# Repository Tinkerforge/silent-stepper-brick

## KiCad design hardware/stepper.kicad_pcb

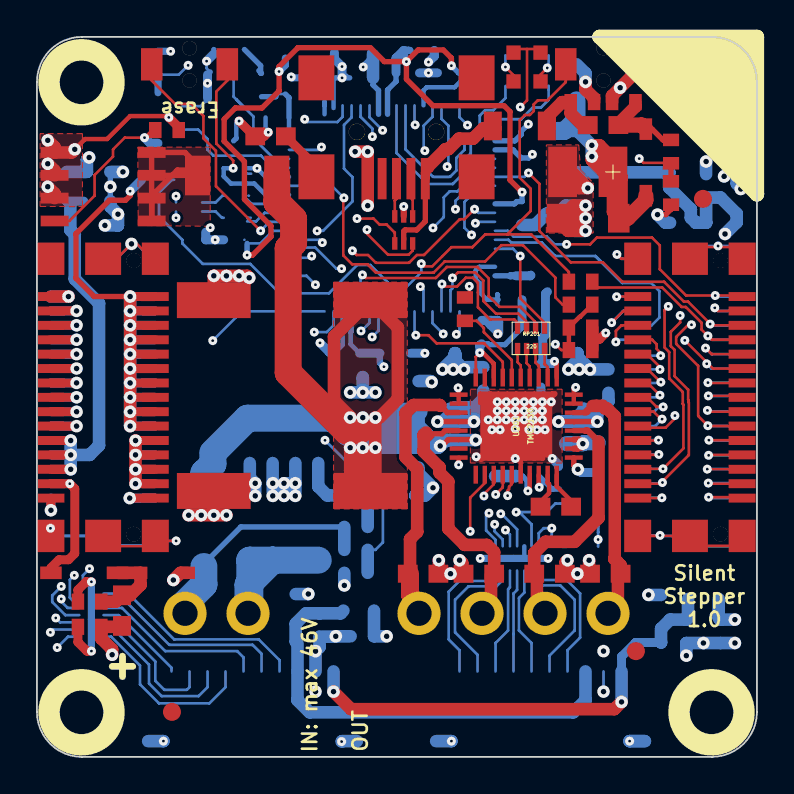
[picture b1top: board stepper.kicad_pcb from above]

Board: 6 copper layers, 40.0 x 40.0 mm, 129 parts (0 on the bottom side), 129 nets.

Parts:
C101, C102, C301, C302, C303, C304, C401, C402, C403, C404: 1µF; C0402E
C103, C104: DNP; C0402E
C201, C209, C217, C218, C503, C506, C507, C508, C510, C511, C512, C513, C515, C517, C518: 100nF; C0402E
C202, C205: 330µF/50V; ELKO_103
C203: 470nF; C0402E
C204, C505, C516: 4.7µF; C0603E
C206, C208, C211, C213: 100nF/50V; C0603E
C207: 22nF/50V-low; C0603E
C210, C212, C214, C216: 470pF/100V; C0603E
C215: 4.7µF/50V; C1206
C501: 100µF; 3528-21
C502, C504: 10µF; C0805
C509: 2.2µF; C0603E
C514: 10µF/10V; C0805
D101: blue; D0603
D102: red; D0603
D201: Z12V; SOD-123
D202, D203: PMEG6045ETPX; SOD-128
D301, D402: ESD5V0D3B-TP; SOD-323
D302: ESD3V3D3B-TP; SOD-323
D401: TVS 3V3; SOD-323
D403, D501: B0520LW-7-F; SOD-123
D502: Z5V; MiniMelf
D503: Z3.3V; MiniMelf
F101: PTC; C1206
FB101, FB102, FB401, FB402: FB; C0603E
FB301, FB302: FILTER; C0603E
FILTER301, FILTER302: Filter-8x; DFN16-33x135
Fiducial_Mark: VAL**; Fiducial_Mark
Fiducial_Mark#2, Fiducial_Mark#3, Fiducial_Mark#4, Fiducial_Mark#5, Fiducial_Mark#6: VAL**; Fiducial_Mark
J101: USB-MINI-B-SMD
J102, J103, J104, J105: DRILL; DRILL_NP
J401, J403: STACK-UP-HIGH; BTB08-ACS-TOP
J402, J404: STACK-DOWN; BTB08-ACS-BTM
L101: 744230900; WE-CNSW-0603
L501: LBR2012T100K; C0805
P201: black; OQ_2P
P202: green; OQ_4P
P301, P302: CON-SENSOR
Q201: AO4438; SOIC-8-MOSFET
Q202: AO4421; SOIC-8-MOSFET
Q203: 2N7002; SOT23GDS
R101, R102: 27; R0402E
R103: 1.8k; R0402E
R104: 2.7k; R0402E
R105: 100; R0402E
R201, R203, R207, R208, R210, R213, R401: 1k; R0402E
R202, R204, R206: 10k; R0402E
R205: 100k; R0402E
R209: FB; C0402E
R211: 2R2; R0402E
R212: 3.9k; R0402E
R214, R215: 0.12/0.5W; R1206
R216: 220; R0402E
R501: 1R0; R0402E
RP101, RP301: 1k; 4X0603
RP201: 220; 4X0402
SW101: Reset; TACT-SWITCH
SW102: Erase; TACT-SWITCH
U101: AT91SAM3SXB; LQFP64
U102: 82400152; SOT563-SPEC
U201: TMC2130; QFN36_5X6
U501: LD1117; SOT-223
VAL: WEEE_7mm_back
VAL#2: CE_5mm
X101: 16Mhz; CRYSTAL_3225

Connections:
3V3: C302.1, C401.1, C502.1, C503.1, C505.1, C506.1, C507.1, C508.1, C514.1, C515.1, C518.1, D101.1, D102.1, D503.2, FB302.1, FB401.1, FILTER301.14, J401.20, RP301.1, RP301.2, RP301.3, RP301.4, SW102.2, U101.1, U101.7, U101.18, U101.45, U101.58, U501.2
BRICKLET-I2C-SCL: FILTER301.16, FILTER302.16, RP301.8, U101.36
BRICKLET-I2C-SDA: FILTER301.15, FILTER302.15, RP301.5, U101.43
BRICKLET-IO0_0/AD0: FILTER301.10, U101.3
BRICKLET-IO0_1: FILTER301.11, U101.5
BRICKLET-IO0_2/PWM0: FILTER301.12, U101.48
BRICKLET-IO0_3: FILTER301.13, U101.25
BRICKLET-IO1_0/AD1: FILTER302.13, U101.4
BRICKLET-IO1_1: FILTER302.12, U101.6
BRICKLET-IO1_2/PWM1: FILTER302.11, U101.47
BRICKLET-IO1_3: FILTER302.10, U101.19
M1: C216.2, P202.1, U201.13
M2: C214.2, P202.2, U201.15
M3: C212.2, P202.3, U201.32
M4: C210.2, P202.4, U201.34
unnamed: C102.1, F101.1, FB101.2
unnamed: C201.2, R209.2, R210.1, U201.8, U201.10
unnamed: C203.1, R211.1, U201.26
unnamed: C204.1, R211.2, U201.25
unnamed: C207.1, U201.27
unnamed: C207.2, U201.28
unnamed: C208.2, U201.29
unnamed: C209.2, R212.1, R213.2, U201.23
unnamed: C217.2, R214.2, U201.14
unnamed: C218.2, R215.2, U201.33
unnamed: C303.1, D301.2, FB301.2, P301.1, P302.1
unnamed: C304.1, D302.2, FB302.2, P301.3, P302.3
unnamed: C403.1, D401.2, D403.1, FB401.2
unnamed: C404.1, D402.2, FB402.2, J403.22, J403.24, J403.26, J404.22, J404.24, J404.26
unnamed: C509.1, C510.1, C511.1, C512.1, C513.1, L501.1, U101.8, U101.12, U101.24, U101.54
unnamed: C516.1, R501.1
unnamed: C517.1, L501.2, R501.2, U101.64
unnamed: D101.2, RP101.1
unnamed: D102.2, RP101.4
unnamed: D201.2, Q201.G, R205.2
unnamed: D202.1, Q202.D
unnamed: D203.1, P201.1, R205.1, R206.1
unnamed: D403.2, J403.28, J404.28
unnamed: F101.2, J101.1, U102.5
unnamed: FB102.2, J101.6
unnamed: FILTER301.1, P301.4
unnamed: FILTER301.2, P301.5
unnamed: FILTER301.3, P301.6
unnamed: FILTER301.4, P301.10
unnamed: FILTER301.5, P301.9
unnamed: FILTER301.6, P301.8
unnamed: FILTER301.7, P301.7
unnamed: FILTER302.1, P302.4
unnamed: FILTER302.2, P302.5
unnamed: FILTER302.3, P302.6
unnamed: FILTER302.4, P302.7
unnamed: FILTER302.5, P302.8
unnamed: FILTER302.6, P302.9
unnamed: FILTER302.7, P302.10
unnamed: J101.2, U102.1
unnamed: J101.3, U102.3
unnamed: J401.6, J402.8
unnamed: J401.7, J402.7, R401.1
unnamed: J401.8, J402.10
unnamed: J401.10, J402.12
unnamed: J401.12, J402.14
unnamed: J401.13, J402.13
unnamed: J401.14, J402.16
unnamed: J401.15, J402.15
unnamed: J401.16, J402.18
unnamed: J401.17, J402.17
unnamed: J401.18, J402.20
unnamed: J401.21, J402.21
unnamed: J401.22, J402.22
unnamed: J401.23, J402.23
unnamed: J401.24, J402.24
unnamed: J401.25, J402.25
unnamed: J401.27, J402.27
unnamed: J401.29, J402.29
unnamed: J401.30, J402.30
unnamed: J403.29, J404.29
unnamed: J403.30, J404.30
unnamed: L101.1, R102.1
unnamed: L101.2, U102.4
unnamed: L101.3, U102.6
unnamed: L101.4, R101.1
unnamed: P201.2, Q201.D
unnamed: Q202.G, Q203.D, R204.1
unnamed: R101.2, U101.56
unnamed: R102.2, U101.57
unnamed: R105.1, U101.32
unnamed: R216.2, U201.6
unnamed: RP101.5, U101.10
unnamed: RP101.8, U101.9
unnamed: RP201.5, U201.5
unnamed: RP201.6, U201.4
unnamed: RP201.7, U201.3
unnamed: RP201.8, U201.2
unnamed: SW102.1, U101.55
PWR-CLK: R105.2, R201.1, U201.1
PWR-CS: RP201.1, U101.29
PWR-DAC-VREF: R213.1, U101.59
PWR-DIAG0: U101.52, U201.20
PWR-DIAG1: U101.42, U201.21
PWR-DIR: U101.38, U201.7
PWR-ENABLE: U101.37, U201.22
PWR-SCK: RP201.2, U101.44
PWR-SDI: RP201.3, U101.34
PWR-SDO: RP201.4, U101.35
PWR-STEP: R216.1, U101.20
PWR-SW-3V3: R209.1, U101.31
PWR-VEXT: R206.2, R207.1, U101.13
PWR-VSTACK: R202.2, R203.1, U101.16
PWR-VSTACK-SW: Q203.G, R208.2, U101.41
STACK-DETECT/JTAG-TMS: J401.9, J402.9, U101.51
STACK-I2C-SCL/JTAG-TDO: J401.4, J402.4, U101.49
STACK-I2C-SDA/JTAG-TDI: J401.2, J402.2, U101.33
STACK-INT: J401.19, J402.19, U101.63
STACK-PGND: C101.2, C102.2, C103.2, C104.2, C201.1, C202.2, C203.2, C204.2, C205.2, C206.2, C209.1, C210.1, C211.2, C212.1, C213.2, C214.1, C215.2, C216.1, C217.1, C218.1, C301.2, C302.2, C303.2, C304.2, C401.2, C402.2, C403.2, C404.2, C501.2, C502.2, C503.2, C504.2, C505.2, C506.2, C507.2, C508.2, C509.2, C510.2, C511.2, C512.2, C513.2, C514.2, C515.2, C516.2, C517.2, C518.2, D201.1, D301.1, D302.1, D401.1, D402.1, D502.1, D503.1, FB102.1, FILTER301.EXP, FILTER302.14, FILTER302.EXP, J101.5, J401.EP, J402.EP, J403.1, J403.3, J403.5, J403.7, J403.9, J403.11, J403.13, J403.15, J403.17, J403.19, J403.21, J403.23, J403.25, J403.27, J403.EP, J404.1, J404.3, J404.5, J404.7, J404.9, J404.11, J404.13, J404.15, J404.17, J404.19, J404.21, J404.23, J404.25, J404.27, J404.EP, P301.2, P301.EP, P302.2, P302.EP, Q201.S, Q203.S, R104.1, R201.2, R203.2, R207.2, R208.1, R210.2, R212.2, R214.1, R215.1, SW101.2, U101.2, U101.17, U101.46, U101.60, U102.2, U201.11, U201.12, U201.18, U201.24, U201.35, U201.36, U201.EXP, U501.1, X101.3
STACK-PVCC: J403.2, J403.4, J403.6, J403.8, J403.10, J403.12, J403.14, J403.16, J403.18, J403.20, J404.2, J404.4, J404.6, J404.8, J404.10, J404.12, J404.14, J404.16, J404.18, J404.20, Q202.S, R202.1, R204.2
STACK-RESET: R401.2, SW101.1, U101.39
STACK-SER-RXD: J401.26, J402.26, U101.11
STACK-SER-TXD: J401.28, J402.28, U101.14
STACK-SPI-MISO: J401.1, J402.1, U101.27
STACK-SPI-MOSI: J401.3, J402.3, U101.22
STACK-SPI-SCLK: J401.5, J402.5, U101.21
STACK-SPI-SELECT: J402.6, U101.28
STACK-SYNC/JTAG-TCK: J401.11, J402.11, U101.53
USB-DETECT: R103.2, R104.2, U101.26
VEE: C202.1, C205.1, C206.1, C208.1, C211.1, C213.1, C215.1, D202.2, D203.2, U201.16, U201.30, U201.31
VSTACK: C301.1, C402.1, C501.1, C504.1, D501.2, D502.2, FB301.1, FB402.1, U501.3
VUSB: C101.1, D501.1, FB101.1, R103.1
XIN: C104.1, U101.62, X101.2
XOUT: C103.1, U101.61, X101.1

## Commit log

2015-09-15 add hardware files of silent stepper brick prototype
2015-09-15 add datasheet of TMC2100 and copied and modified stepper firmware
2015-09-16 working demo, configuration hardcoded
2015-11-26 fix text positions
2015-12-17 minor changes
2015-12-17 Fix names, versions, etc
2015-12-23 Add Silent Stepper configuration API
2016-02-08 update to new library settings
2016-02-09 fix tf logo, remove current measurement
2016-02-09 missing commit, remove current measurement
2016-02-09 Add WIP marker
2016-02-09 Add .gitignore
2016-02-11 fix wrong bricklet select voltages
2016-02-11 detail routing improvements
2016-02-12 move leds from border, delete to near doku
2016-02-22 fix led config
2016-02-24 remove motor capacitors
2016-02-25 uncomitted hardware changes
2016-02-25 remove cfg3, add clk connection, imprv gnd routing, 3v3 switchable
2016-06-13 demo stepper mode switching
2016-06-22 changed to tmc2130
2016-09-06 mark: remove 3v3 mosfet
2016-09-16 Basic adjustments for SPI configuration
2016-09-28 Seperate TCM2130 configuration from general stepper handling
2016-09-28 Implement stepping for dedge=1
2016-09-28 Remove unused function declarations
2016-10-04 remove unnecessary signals, add external clock
2016-10-05 change driver type to tmc2130
2016-10-13 Make register write async
2016-10-14 Disable DMA support for now (not working)
2016-10-17 change clock series resistor 1k->470
2016-10-18 Add driver status support
2016-10-21 Handle spi read overrun
2016-10-21 turn DMA off after deselect
2016-10-21 Properly handle enable pin after active changes from false to true
2016-10-21 Add active pin handle variables
2016-11-24 Remove unused function
2016-11-25 swap pins, add series resistors, add clock pi filter
2016-12-02 add pdfs
2016-12-05 Add system timer utility file include to Makefile
2016-12-06 adapt software to current hardware version Change pins of: * leds * spi cs * enable pins
2016-12-15 version before changing to 6 layers
2016-12-15 change to 6 layer layout
2016-12-16 change routing, remove pi filter
2016-12-19 drc check
2017-01-06 Add COM_MESSAGE_USER_LAST_FID define (needed for newest bricklib)
2017-01-09 update fiducials
2017-01-17 change default design to 6layer design
2017-01-26 Add human readable parameters for basic config function
2017-01-26 Use correct delay for one second at 12.8MHz
2017-01-26 Add current output default value (800mA)
2017-01-26 Remove obsolete FIXME comment
2017-01-26 Use correct VREF scaling for maximum current configuration
2017-04-18 add schematics
2017-04-19 The driver IC is called TMC2130, not TCM2130...
2017-04-19 Fix typo
2017-04-19 Remove debug
2017-04-19 Add examples
2017-04-21 Fix examples
2017-04-21 Add 3d information (tbc)
2017-04-21 Add most of the 3d information
2017-04-25 Change D102 to red 3d model
2017-04-25 Change connection footprints
2017-04-28 Fix reordered component paths
2017-04-28 Add Elkos and 4x0603 3d models
2017-05-11 Add support for co-mcu Bricklets
2017-05-11 Add changelog
2017-05-11 Fix changelog
2017-05-16 Remove bogus stepper current calculation.
    This erroneously copied from old Stepper Brick.
2017-05-16 Calculate motor current from user set motor run current and actual motor current register.
2017-05-16 Always return 0 for current if stepper is off
2017-05-16 Increase version, add changelog for 2.0.2
2017-05-16 Add ref for last changelog entry
2017-05-17 Fix LED color
2017-06-02 octave: Use javaObject instead of deprecated java_new
2017-06-09 Add missing 3d information
2017-06-09 Add 3d model (*.step and *.FCStd)
2017-06-16 Add heatsink to 3d model
2017-06-28 Update changelog and version
2017-06-28 Add tag ref to changelog
2017-12-05 Remove initial USB enumeration (now done in bricklib)
2017-12-05 Increase firmware version, update changelog
2017-12-07 mathematica: Also generate .nb files
2017-12-12 Rename *.step & *.FCStd files
2017-12-12 Remove unused include
2017-12-12 Remove unused variable
2017-12-13 Add date and ref to changelog
2018-01-11 Increase version number (message duplication bug fix through bricklib)
2018-01-11 Add ref to changelog
2018-02-19 javascript: Close div tag correctly
2018-02-20 Cleanup KiCad libraries config
    Ensure LibDir=kicad-libraries and LibName1=tinkerforge.
    Remove special library.
2018-04-27 Update version and changelog
2018-04-27 Add git ref to changelog
2018-05-24 perl: Use strict in examples
2018-05-28 mathematica: Fix namespace
2018-05-29 Minor example tweaks
2018-06-28 Fix readme
2018-07-11 Add Makefile with docker support
2018-07-11 Remove obsolete generate_makefile scripts
2018-07-11 Update directory structure and build instructions
2018-07-25 Add new 3d model
2018-07-31 Increase version and update changelog
2018-07-31 Update changelog ref
2018-09-03 Unify spelling in changelog
2018-09-28 vbnet: Remove outdated incomplete marker
2018-11-06 Add rust examples
2018-11-07 rust: Accept host names for ip connection, fix naming inconsistencies
2018-11-07 rust: Rename callback receivers.
2018-12-14 Add go examples.
2018-12-18 go: Change import path.
2018-12-18 go: Change import path again.
2018-12-20 rust: Reformat examples.
2019-01-24 mqtt: Add examples.
2019-01-24 mqtt: Fix example header.
2019-01-24 mqtt: Remove executable bit in example permissions.
2019-01-24 go: Minor example fixes.
2019-01-24 mqtt: Minor example fixes.
2019-02-27 Increase version for new release (changes in bricklib)
2019-02-27 Add rev to changelog
2019-05-14 Update rust examples.
2019-08-22 c: Adapt to bindings changes
2020-01-13 examples: Use python3 input instead of python2 raw_input.
2020-01-13 examples: mqtt: Remove trailing whitespace.
2020-01-14 examples: Use python3 input by default.
2020-03-18 rust: Update to new skeleton
2020-03-20 examples: Properly stop motor before disabling motor power
    Disabling motor power while motor is still running could cause
    hardware damage.
2020-04-07 examples: Add missing imports for sleep calls
2020-04-07 examples: rust: Always block when calling bindings functions.
2020-04-07 examples: rust: Block when calling bindings functions.
2021-05-03 examples: Fix user data passing to callback
2021-10-25 Update KiCad link
    https://www.kicad.org/blog/2021/10/Avoid-links-to-former-kicad-domain/
2022-07-06 Add license files.
2024-02-21 examples/rust: Fix random number generation.

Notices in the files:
hardware/stepper.kicad_pcb:
Licensed under CERN OHL v.1.1
Copyright (©) 2016, B.Nordmeyer
Copyright Tinkerforge GmbH 2016.
This documentation describes Open Hardware and is licensed under the
CERN OHL v. 1.1.
